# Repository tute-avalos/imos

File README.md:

Integral Moto Open System (IMOS)
================================

Introducción
------------

Es un sistema integral y abierto que monitorea y controla las variables de la moto, asociciandose por bluetooth a una aplicación de Android que tiene como objetivo mejorar/reemplazar el panel de instrumentos agregando funcionalidades y estadísticas de uso.

Este proyecto consta de 3 partes:

  * **Hardware** diseñado en [CADSoft Eagle](https://cadsoft.io/).
  * **Firmware** con un microcontrolador AVR de 8-bits escrito en C/C++. 
  * **Software** que es una apk para Android.

Sobre el proeyecto y sus autores
--------------------------------

El proyecto fue originalmente ideado por Fernando Filippetti, estudiante de Ingeniería en Electrónica en la Universidad de Buenos Aires y apasionado de las motos. Haciendo contribuciones mínimas a la realización del hardware, dando alguna que otra idea, el hardware se hizo y la placa fue sometida a pruebas funcionales sobre sus componentes (ensayos de laboratorio) y allí quedo un tiempo.

Por mi parte (Matías S. Ávalos), estaba buscando qué presentar como proyecto final en mi Tecnicatura Superior en Informática Aplicada, entonces le propuse al idéologo de este proyecto que podía ayudarlo a terminar con él. Tanto colaborando en el Firmware como en su idea de poder acceder mediante Bluetooth con un dispositivo móvil a las funcionalidades de la placa.

Tanto Fernando como yo, somos impulsores, promotores y evangelizadores del Hardware y Software Libre. Por eso proponemos que cualquiera que esté leyendo esto y quiera modificar/mejorar o simplemente ver como logramos alguna pequeña cuestión dentro de este proyecto, sea bienvenido a hacer un fork del mismo o contribuir en él.

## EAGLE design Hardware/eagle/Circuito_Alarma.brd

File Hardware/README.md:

Sobre el Hardware de IMOS
=========================

Antes que nada este es un proyecto con espiritu de Hardware y Software Libre, y como tal, estamos abiertos y promovemos la adaptación, mejora u proyectos nuevos basados en este con cualquier fin, educativo y/o comercial siempre y cuando sea noble y dentro del marco de la legalidad.

Esquemático y diseño del PCB
----------------------------

El esquemático y PCB están hechos originalmente por Fernando Filippetti, en [CADSoft Eagle](https://cadsoft.io/), y para su uso comercial debe contar con una licencia extendida por el distribuidor oficial de este software. No nos hacemos responsables por su uso indebido. En un futuro, si el proyecto prospera, nos gustaría traspasarlo con algún Software libre como KiCAD o similar para poder utilizarlo sin restricciones. Cualquier ayuda con este último punto será bienvenida.

Gerbers
-------

Los gerbers generados son con las especificaciones técnicas requeridas por la Facultad de Ingeniería de la Universidad de Buenos Aires (FIBA - UBA) que fueron los que nos proporcionaron la versión física del PCB para este proyecto.

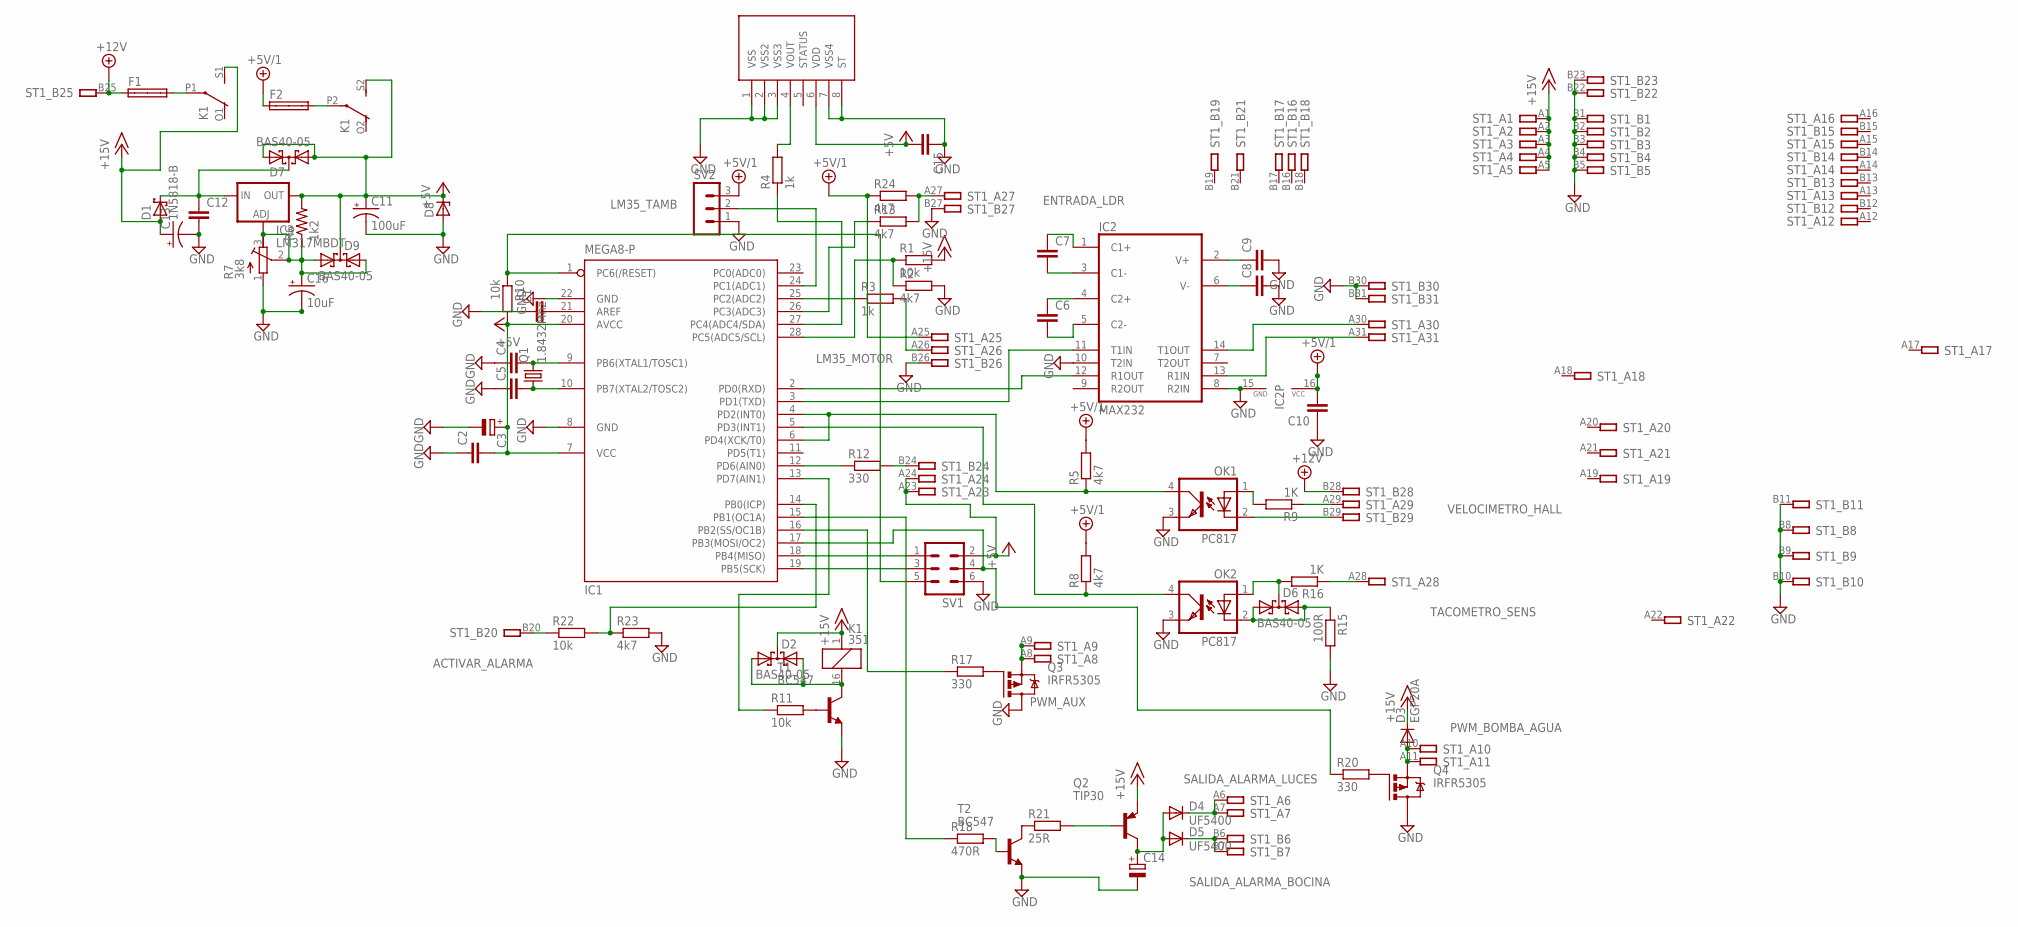
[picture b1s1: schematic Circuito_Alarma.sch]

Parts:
C1, C2, C4, C5, C6, C7, C8, C9, C15: CC1206; C1206
C3, C14: CPOL-EUE2.5-5; E2,5-5
C10, C12: C-EU050-024X044; C050-024X044
C11: 100uF; E2,5-5
C13: CPOL-USE2.5-5; E2,5-5
C16: 10uF; E2,5-5
D1: 1N5818-B; DO41-7.6
D2, D6, D7, D9: BAS40-05; SOT23
D3: EGP20A; DO15-12
D4, D5: UF5400; DO201-15
D8: ZENER-DIODEZD-5; ZDIO-5
F1, F2: SHK20L
IC1: MEGA8-P; DIL28-3
IC2: MAX232; DIL16
IC3: LM317MBDT; DPACK
K1: 351
OK1, OK2: PC817; DIL04
Q1: 1.8432Mhz; TC26H
Q2: TIP30; TO220
Q3, Q4: IRFR5305; D-PAK_TO252AA
R1, R10, R11, R22: 10k; 0204/5
R2, R5, R8, R13, R23, R24: 4k7; 0204/5
R3, R4: 1k; 0204/5
R6: 1k2; M1206
R7: 3k8; RTRIM64W
R9, R16: 1K; 0204/5
R12, R17, R20: 330; 0204/5
R15: 100R; 0204/5
R18: 470R; 0204/5
R21: 25R; 0411/12
ST1: IBM8BIT
SV1: MA03-2
SV2: MA03-1
T1, T2: BC547; TO92
U$1: MMA1260; N5

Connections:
+5V: C2.2, C3.+, C11.+, C15.2, D7.1 (A1), D7.2 (A2), D8.C, D9.3 (C), IC1.7 (VCC), IC1.20 (AVCC), IC3.4 (OUT), K1.S2 (S), R6.2, R10.2, ST1.A23, ST1.A24, SV1.2, U$1.6 (VDD)
+5V/1: C10.2, F2.1A, IC2.16 (VCC), R5.2, R8.2, R24.1, ST1.A25, SV2.3
+12V: F1.1A, ST1.B25, ST1.B28
+15V: C13.+, D1.A, D2.3 (C), D3.C, K1.1, K1.S1 (S), Q2.3 (E), R1.2, ST1.A1, ST1.A2, ST1.A3, ST1.A4, ST1.A5
ACTIVAR_ALARMA: R22.1, ST1.B20
ENTRADA_LDR: R13.2, R24.2, ST1.A27
GND: C1.1, C2.1, C3.-, C4.1, C5.1, C8.2, C9.2, C10.1, C11.-, C12.2, C13.-, C14.-, C15.1, C16.-, D8.A, IC1.8 (GND), IC1.22 (GND), IC2.8 (R2IN), IC2.10 (T2IN), IC2.15 (GND), OK1.3 (EMIT), OK2.3 (EMIT), Q3.4 (D), Q4.4 (D), R2.2, R7.1 (E), R15.2, R23.2, ST1.B1, ST1.B2, ST1.B3, ST1.B4, ST1.B5, ST1.B8, ST1.B9, ST1.B10, ST1.B11, ST1.B22, ST1.B23, ST1.B26, ST1.B27, ST1.B30, ST1.B31, SV1.6, SV2.1, T1.1 (E), T2.1 (E), U$1.1 (VSS), U$1.2 (VSS2), U$1.3 (VSS3), U$1.7 (VSS4), U$1.8 (ST)
LM35_MOTOR: R3.2, ST1.A26
LM35_TAMB: IC1.24 (PC1(ADC1)), SV2.2
unnamed: IC1.18 (PB4(MISO)), SV1.1
unnamed: IC1.19 (PB5(SCK)), SV1.3
unnamed: C4.2, IC1.9 (PB6(XTAL1/TOSC1)), Q1.2
unnamed: C5.2, IC1.10 (PB7(XTAL2/TOSC2)), Q1.1
unnamed: IC1.17 (PB3(MOSI/OC2)), R20.1, SV1.4
unnamed: C1.2, IC1.21 (AREF)
unnamed: IC1.1 (PC6(/RESET)), R10.1, SV1.5
unnamed: IC1.28 (PC5(ADC5/SCL)), R1.1, R2.1
unnamed: IC1.3 (PD1(TXD)), IC2.11 (T1IN)
unnamed: IC1.2 (PD0(RXD)), IC2.12 (R1OUT)
unnamed: C8.1, IC2.6 (V-)
unnamed: C9.1, IC2.2 (V+)
unnamed: C6.1, IC2.4 (C2+)
unnamed: C6.2, IC2.5 (C2-)
unnamed: C7.2, IC2.3 (C1-)
unnamed: C7.1, IC2.1 (C1+)
unnamed: C12.1, D1.C, D7.3 (C), IC3.3 (IN)
unnamed: R4.2, U$1.4 (VOUT)
unnamed: IC1.26 (PC3(ADC3)), R13.1
unnamed: IC1.25 (PC2(ADC2)), R3.1
unnamed: F2.2A, K1.P2
unnamed: IC1.15 (PB1(OC1A)), R18.1
unnamed: IC1.5 (PD3(INT1)), OK2.4 (COL), R8.1
unnamed: IC1.4 (PD2(INT0)), IC1.6 (PD4(XCK/T0)), OK1.4 (COL), R5.1
unnamed: D2.1 (A1), D2.2 (A2), K1.16 (2), T1.3 (C)
unnamed: R11.2, T1.2 (B)
unnamed: IC1.16 (PB2(SS/OC1B)), R17.1
unnamed: R9.1, ST1.A29
unnamed: R16.1, ST1.A28
unnamed: IC1.13 (PD7(AIN1)), R11.1
unnamed: D6.3 (C), OK2.1 (A), R16.2
unnamed: IC2.14 (T1OUT), ST1.A30
unnamed: IC2.13 (R1IN), ST1.A31
unnamed: C16.+, D9.1 (A1), D9.2 (A2), IC3.1 (ADJ), R6.1, R7.2 (S), R7.3 (A)
unnamed: R12.2, ST1.B24
unnamed: IC1.12 (PD6(AIN0)), R12.1
unnamed: F1.2A, K1.P1
unnamed: OK1.1 (A), R9.2
unnamed: Q3.1 (G), R17.2
unnamed: R18.2, T2.2 (B)
unnamed: IC1.14 (PB0(ICP)), R22.2, R23.1
unnamed: R21.1, T2.3 (C)
unnamed: IC1.27 (PC4(ADC4/SDA)), R4.1
unnamed: Q4.1 (G), R20.2
unnamed: Q2.1 (B), R21.2
unnamed: C14.+, D4.A, D5.A, Q2.2 (C)
PWM_AUX: Q3.3 (S), ST1.A8, ST1.A9
PWM_BOMBA_AGUA: D3.A, Q4.3 (S), ST1.A10, ST1.A11
SALIDA_ALARMA_BOCINA: D5.C, ST1.B6, ST1.B7
SALIDA_ALARMA_LUCES: D4.C, ST1.A6, ST1.A7
TACOMETRO_SENS: D6.1 (A1), D6.2 (A2), OK2.2 (C), R15.1
VELOCIMETRO_HALL: OK1.2 (C), ST1.B29

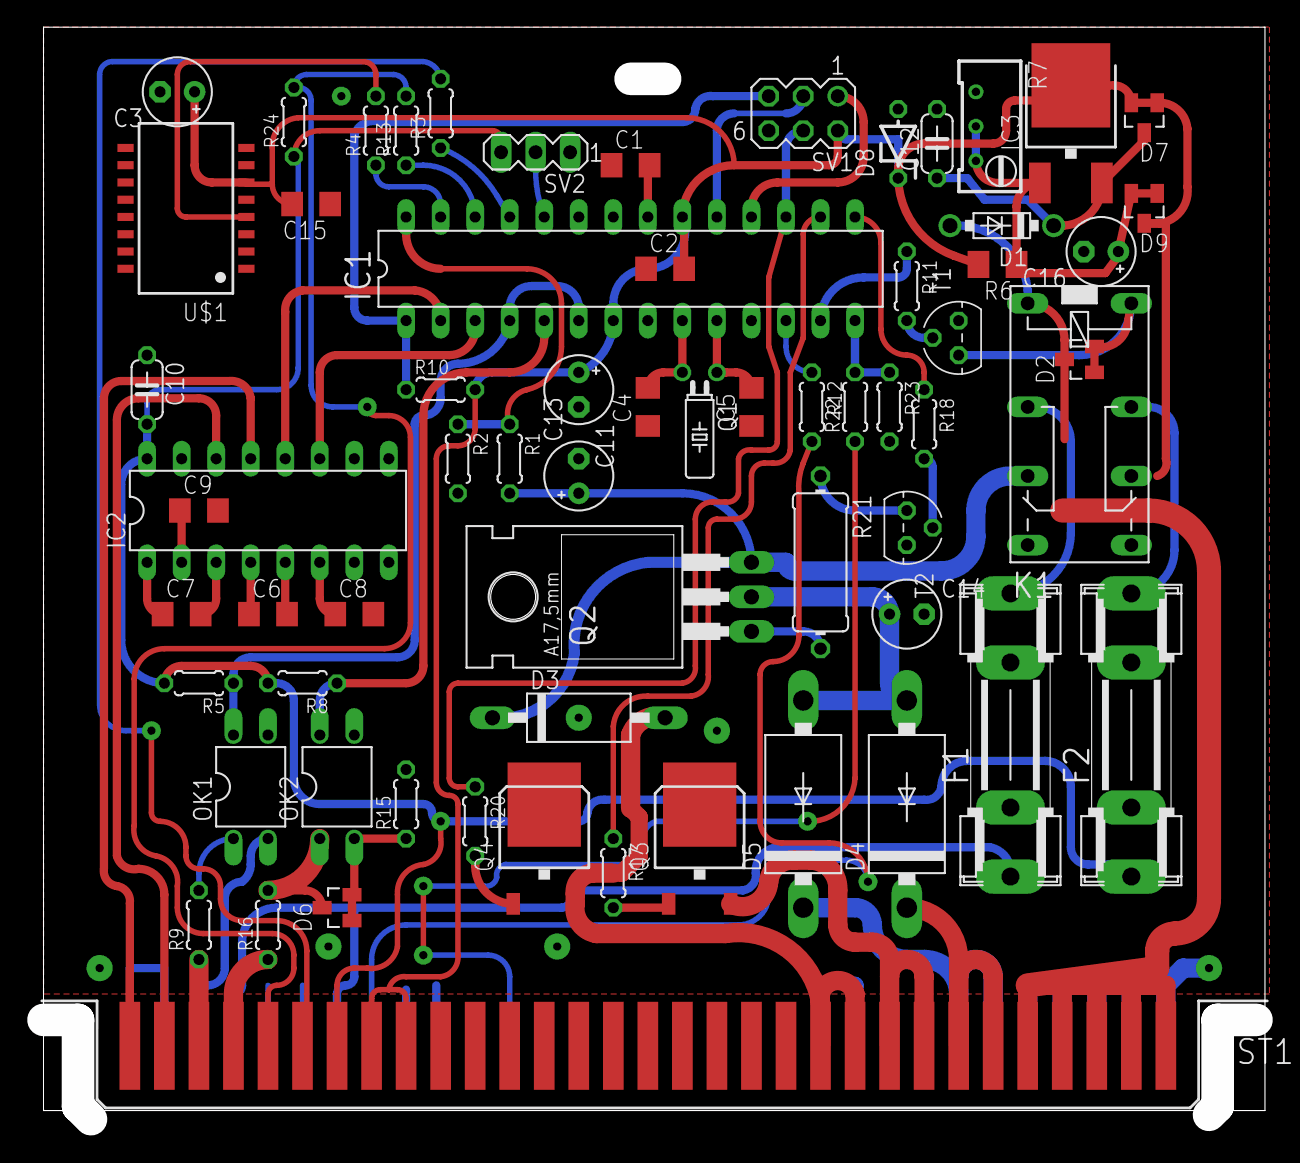
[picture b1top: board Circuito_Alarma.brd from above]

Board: 2 copper layers, 89.2 x 79.1 mm, 66 parts (0 on the bottom side), 61 nets.

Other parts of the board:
DRILEGEND: DRILEGEND

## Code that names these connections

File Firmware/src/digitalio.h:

/*******************************************************************************
 * 
 * Copyright (C) 2017 Matías Sebastián Ávalos <msavalos@gmail.com>
 *
 * This file is part of Integral Moto Open System (IMOS).
 *
 *    Integral Moto Open System (IMOS) is free software: you can 
 *    redistribute it and/or modify it under the terms of the GNU
 *    General Public License as published by the Free Software
 *    Foundation, either version 3 of the License, or (at your option)
 *    any later version.
 *
 *    Integral Moto Open System (IMOS) is distributed in the hope that
 *    it will be useful, but WITHOUT ANY WARRANTY; without even the 
 *    implied warranty of MERCHANTABILITY or FITNESS FOR A PARTICULAR 
 *    PURPOSE. See the GNU General Public License for more details.
 *
 *    You should have received a copy of the GNU General Public License
 *    along with Integral Moto Open System (IMOS).
 *    If not, see <http://www.gnu.org/licenses/>.
 *  
 * 
 * Fork me on GitHub: https://github.com/tute-avalos/imos/
 * 
 ******************************************************************************/
/**
 * @file digitalio.h
 * @author Matías S. Ávalos <msavalos@gmail.com>
 * @version v0.1
 * @date 06/01/2017 (dd/mm/yyyy)
 * @brief Manejo de entradas y salidas digitales.
 * 
 * @details
 *  Inspirado en Arduino, pero en vez de usar números de pines numericos, 
 * se usan los nombres originales del integrado.
 *
 */
/** @defgroup Digital_IO Digital I/O implementation
 * @ingroup API
 */
#ifndef __DIGITALIO_H__
#define __DIGITALIO_H__

#ifdef __cplusplus
extern "C" {
#endif

/** @addtogroup Digital_IO
 * @{
 */
//#define _PORTA  (1 << 4)
#define _PORTB  (1 << 5)    //!< @brief Selección para el PORTB.
#define _PORTC  (1 << 6)    //!< @brief Selección para el PORTC.
#define _PORTD  (1 << 7)    //!< @brief Selección para el PORTD.

#define _PIN0   0   //!< @brief Selección del pin 0.
#define _PIN1   1   //!< @brief Selección del pin 1.
#define _PIN2   2   //!< @brief Selección del pin 2.
#define _PIN3   3   //!< @brief Selección del pin 3.
#define _PIN4   4   //!< @brief Selección del pin 4.
#define _PIN5   5   //!< @brief Selección del pin 5.
#define _PIN6   6   //!< @brief Selección del pin 6.
#define _PIN7   7   //!< @brief Selección del pin 7.

#define _PB0 (_PORTB | _PIN0)    //!< @brief Pin PORTB0.
#define _PB1 (_PORTB | _PIN1)    //!< @brief Pin PORTB1.
#define _PB2 (_PORTB | _PIN2)    //!< @brief Pin PORTB2.
#define _PB3 (_PORTB | _PIN3)    //!< @brief Pin PORTB3.
#define _PB4 (_PORTB | _PIN4)    //!< @brief Pin PORTB4.
#define _PB5 (_PORTB | _PIN5)    //!< @brief Pin PORTB5.
#define _PB6 (_PORTB | _PIN6)    //!< @brief Pin PORTB6.
#define _PB7 (_PORTB | _PIN7)    //!< @brief Pin PORTB7.

#define _PC0 (_PORTC | _PIN0)    //!< @brief Pin PORTC0.
#define _PC1 (_PORTC | _PIN1)    //!< @brief Pin PORTC1.
#define _PC2 (_PORTC | _PIN2)    //!< @brief Pin PORTC2.
#define _PC3 (_PORTC | _PIN3)    //!< @brief Pin PORTC3.
#define _PC4 (_PORTC | _PIN4)    //!< @brief Pin PORTC4.
#define _PC5 (_PORTC | _PIN5)    //!< @brief Pin PORTC5.
#define _PC6 (_PORTC | _PIN6)    //!< @brief Pin PORTC6.
#define _PC7 (_PORTC | _PIN7)    //!< @brief Pin PORTC7.

#define _PD0 (_PORTD | _PIN0)    //!< @brief Pin PORTD0.
#define _PD1 (_PORTD | _PIN1)    //!< @brief Pin PORTD1.
#define _PD2 (_PORTD | _PIN2)    //!< @brief Pin PORTD2.
#define _PD3 (_PORTD | _PIN3)    //!< @brief Pin PORTD3.
#define _PD4 (_PORTD | _PIN4)    //!< @brief Pin PORTD4.
#define _PD5 (_PORTD | _PIN5)    //!< @brief Pin PORTD5.
#define _PD6 (_PORTD | _PIN6)    //!< @brief Pin PORTD6.
#define _PD7 (_PORTD | _PIN7)    //!< @brief Pin PORTD7.

#define INPUT       0x00    //!< @brief Configurado como entrada.
#define OUTPUT      0x01    //!< @brief Configurado como salida.
#define TRISTATE    0x00    //!< @brief Configurado en Tri-state (Hi-Z)
#define PULLUP      0x02    //!< @brief Configurado con pull-up.

#define LOW     0   //!< @brief Valor/estado del pin en "bajo".
#define HIGH    1   //!< @brief Valor/estado del pin en "alto".
/**
 * @}
 */

/**
 * @brief Indica si el pin es de entrada o salida.
 * @param pin Pin del puerto que se desea configurar.
 * @param mode Modo en que se desea configurar 
 * @ingroup Digital_IO
 */
void pinMode(uint8_t pin, uint8_t mode);

/**
 * @brief Pone un estado en un pin que esté configurado como salida.
 * @param pin Pin al que se desea cambiar el estado.
 * @param state Estado en que se desea poner el pin.
 * @ingroup Digital_IO
 */
void digitalWrite(uint8_t pin, uint8_t state);

/**
 * @brief Estado actual del pin que está configurado como entrada.
 * @param pin Pin que se deasea leer.
 * @return state en que está el pin actualmente.
 * @ingroup Digital_IO
 */
uint8_t digitalRead(uint8_t pin);

#ifdef __cplusplus
}
#endif

#endif // __DIGITALIO_H__
 
 

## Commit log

2016-12-21 Primer commiteada
2016-12-23 Algunas documentaciones y aclaraciones
2016-12-23 Removidos los .PS
2016-12-27 correcciones de hardware
2016-12-28 Mejora de la documentación
2017-01-07 firmware api v0.1
2017-01-07 Faltaba licencia en fuse.c
2017-01-09 SysClk v0.1
2017-01-17 Modificaciones en la clase SystemClock
2017-01-30 Tachometer implementation
